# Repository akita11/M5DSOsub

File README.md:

# M5DSOsub

M5StackBasicを簡易的なオシロにするアダプタです。M5Stackを簡易オシロにするソフトウエアはいくつかあります（例えば[M5Stack-ESP32-Oscilloscope](https://github.com/botofancalin/M5Stack-ESP32-Oscilloscope)や[M5Stackオシロスコープ](https://goji2100.com/blog/?p=967)など）。いずれもM5StackのBOTTOM（底板）に出ているアナログ入力(GPIO36/35)を入力として使っています。

M5StackBasicのBOTTOMコネクタにこのアダプタを差し込むことで、これらのソフトウエアを使って、簡易オシロにすることができます。入力保護回路つきで、ショートピン切り替えで1/10アッテネータを使用できます。

※これらの2つのソフトウエアは、ArduinoIDEで使えるバージョンのESP32用ライブラリ(ESP-IDF)では再起動を繰り返す挙動があるようです。[M5Stack-ESP32-Oscilloscopeのほうは、Issueに上がっている修正](https://github.com/botofancalin/M5Stack-ESP32-Oscilloscope/issues/2)を行うことで、この問題を回避できます。

## 使い方

M5StackBasicのBOTTOMのコネクタに、このように接続します。

2つのメスソケットがCh1, Ch2の入力端子（と基準電圧のGND）です。ジャンパワイヤ等で測定対象の回路に接続します。

またその横のピン（x10と表記）にショートピンをはめると、各チャンネルの入力信号が10倍に増幅されてM5Stackに与えられます。つまり1/10倍の微小な信号電圧を扱うことができます。

### パルス出力

信号チェック等に使える2つの出力波形がOut1, Out2の２つのピンソケットに出力されています。Out1はGPIO2、Out2はGPIO5（またはJP1のハンダジャンパを切り替えることでGPIO26）に接続されています。

## Author

Junichi Akita (akita@ifdl.jp, @akita11)

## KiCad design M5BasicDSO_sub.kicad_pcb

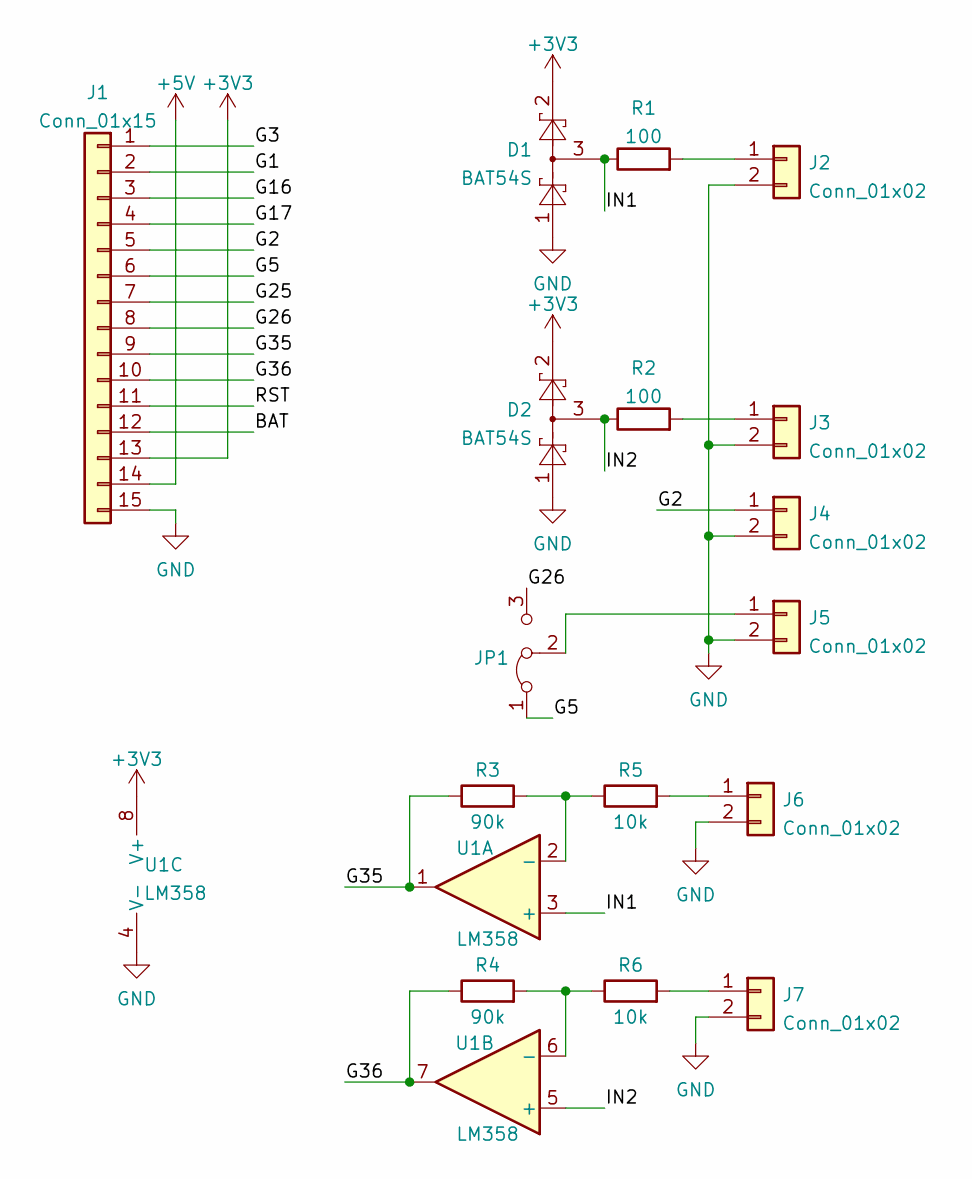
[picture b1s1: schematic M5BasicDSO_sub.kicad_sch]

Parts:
D1, D2: BAT54S; SOT-23
J1: Conn_01x15; PinHeader_1x15_P2.54mm_Vertical
J2, J3, J4, J5, J6, J7: Conn_01x02; PinHeader_1x02_P2.54mm_Vertical
JP1: Jumper_3_Bridged12; SolderJumper-3_P1.3mm_Bridged12_Pad1.0x1.5mm
R1, R2: 100; R_0603_1608Metric
R3, R4: 90k; R_0603_1608Metric
R5, R6: 10k; R_0603_1608Metric
U1: LM358; SO-8_5.3x6.2mm_P1.27mm

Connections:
+3V3: D1.2, D2.2, J1.13, U1.8 (V+)
+5V: J1.14
/BAT: J1.12
/G1: J1.2
/G2: J1.5, J4.1
/G3: J1.1
/G5: J1.6, JP1.1 (A)
/G16: J1.3
/G17: J1.4
/G25: J1.7
/G26: J1.8, JP1.3 (B)
/G35: J1.9, R3.1, U1.1
/G36: J1.10, R4.1, U1.7
/IN1: D1.3, R1.1, U1.3 (+)
/IN2: D2.3, R2.1, U1.5 (+)
/RST: J1.11
GND: D1.1, D2.1, J1.15, J2.2, J3.2, J4.2, J5.2, J6.2, J7.2, U1.4 (V-)
unnamed: J2.1, R1.2
unnamed: J3.1, R2.2
unnamed: J5.1, JP1.2 (C)
unnamed: J6.1, R5.2
unnamed: J7.1, R6.2
unnamed: R3.2, R5.1, U1.2 (-)
unnamed: R4.2, R6.1, U1.6 (-)

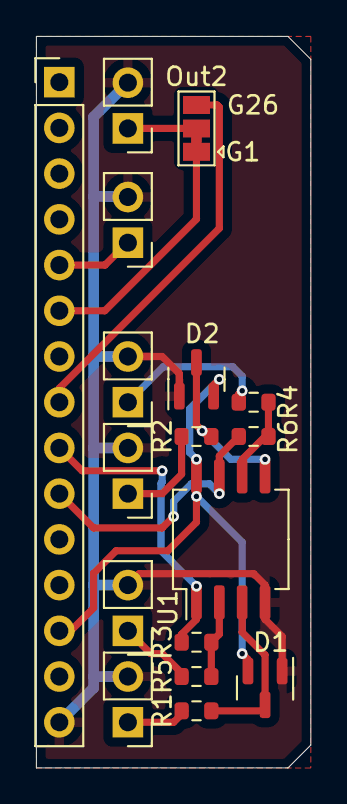
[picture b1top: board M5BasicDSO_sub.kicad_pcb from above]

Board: 2 copper layers, 15.2 x 40.6 mm, 17 parts (0 on the bottom side), 16 nets.

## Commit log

2023-12-24 README.md を更新
2024-01-05 update config photo
